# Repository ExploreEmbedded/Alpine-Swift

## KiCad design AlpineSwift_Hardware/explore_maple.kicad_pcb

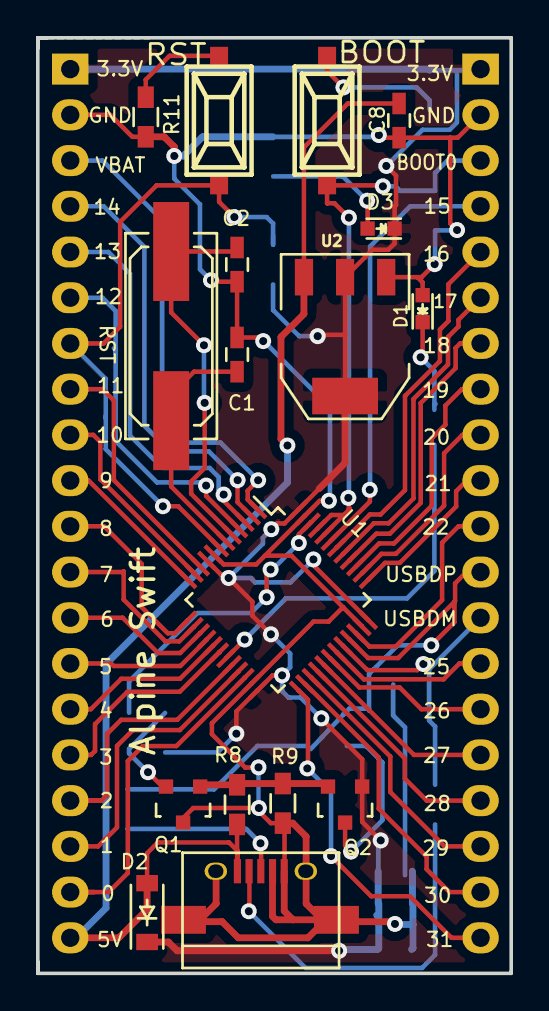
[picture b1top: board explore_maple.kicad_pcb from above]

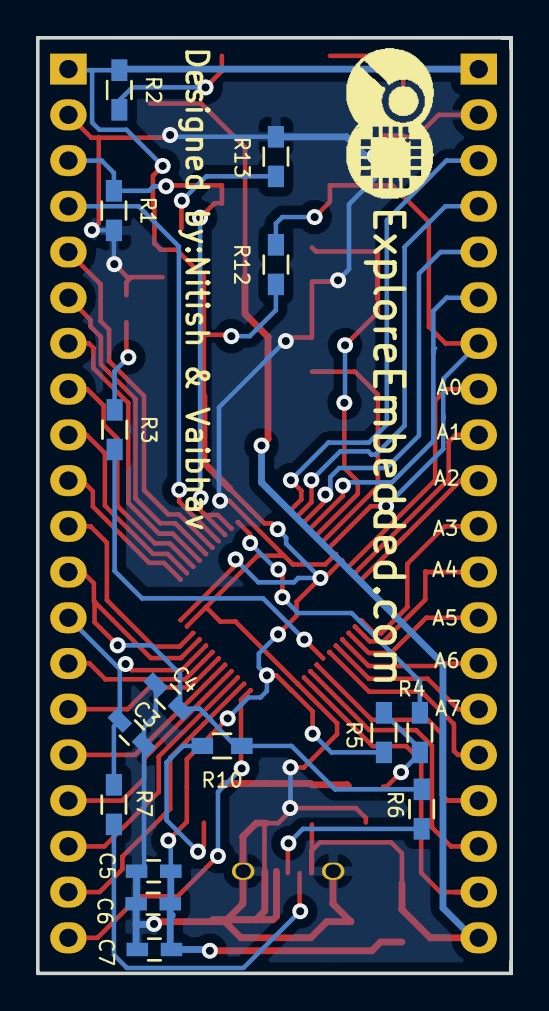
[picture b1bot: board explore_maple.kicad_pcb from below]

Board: 2 copper layers, 26.3 x 52.0 mm, 35 parts (16 on the bottom side), 51 nets.

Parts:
8MHZ1: CRYSTAL; Q_49U3HMS
BOOT: SPST; smd_push
C1, C2: 18pF; C_0603_HandSoldering
C3, C4: 47pf; C_0603_HandSoldering
C5, C6, C7: .1uF; C_0603_HandSoldering
C8: 100uF; C_0603_HandSoldering
CON1: USB-MICRO-B; USB_Micro-B
D1, D3: LED; LED-0603
D2: DIODE; SOD-123
LOGO: LOGO (2)
P1, P2: CONN_01X20; Pin_Header_Straight_1x20
Q1, Q2: BC547; SOT-23
R1, R8, R12: 10K; R_0603_HandSoldering
R2, R3, R4, R11: 1K; R_0603_HandSoldering
R5: 47K; R_0603_HandSoldering
R6, R7: 22; R_0603_HandSoldering
R9: 36K; R_0603_HandSoldering
R10: 1.5K; R_0603_HandSoldering
R13: 470; R_0603_HandSoldering
RST: SPST; smd_push
U1: STM32F103C8; LQFP-48_7x7mm_Pitch0.5mm
U2: LMNEW; SOT-223

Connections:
+3.3VP: C5.2, C6.2, C7.2, D2.1, D3.1, P1.1, P2.1, Q2.1, R2.1, R5.2, R12.1, U1.9, U1.24, U1.36, U1.48, U2.2, U2.4
+5V: C8.1, CON1.1, D2.2, P1.20, R8.2, U2.3
/10: P1.8, U1.10
/11: P1.9, U1.11
/12: P1.10, U1.12
/13: P1.11, U1.13
/14: P1.12, U1.14
/15: P1.13, U1.15
/16: P1.14, U1.16
/17: P1.15, U1.17
/25: P2.20, U1.25
/26: P2.19, U1.26
/27: P2.18, U1.27
/28: P2.17, U1.28
/37: P2.10, U1.37
/38: P2.9, U1.38
/39: P2.8, U1.39
/40: P2.7, U1.40
/41: P2.6, U1.41
/42: P2.5, U1.42
/43: P2.4, U1.43
/44: BOOT.1, P2.3, R1.1, U1.44, U1.45
/DISC: R4.2, U1.46
/OSC_IN: 8MHZ1.2, C2.1, U1.5
/OSC_OUT: 8MHZ1.1, C1.1, U1.6
/RESET: P1.7, R12.2, RST.2, U1.7
/USB_DM: C3.1, P2.13, R7.1, U1.32
/USB_DP: C4.1, P2.12, R6.1, R10.1, U1.33
GND: C1.2, C2.2, C3.2, C4.2, C5.1, C6.1, C7.1, C8.2, CON1.4, CON1.5, CON1.6, CON1.7, CON1.8, CON1.9, D1.2, P1.2, P2.2, Q1.3, R1.2, R9.1, R11.2, R13.2, U1.8, U1.23, U1.35, U1.47, U2.1
unnamed: BOOT.2, R2.2
unnamed: CON1.2, R7.2
unnamed: CON1.3, R6.2
unnamed: D1.1, R3.1
unnamed: D3.2, R13.1
unnamed: P1.3, U1.1
unnamed: P1.4, U1.2
unnamed: P1.5, U1.3
unnamed: P1.6, U1.4
unnamed: P1.16, U1.18
unnamed: P1.17, U1.20
unnamed: P1.18, U1.21
unnamed: P1.19, U1.22
unnamed: P2.11, U1.34
unnamed: P2.14, U1.31
unnamed: P2.15, U1.30
unnamed: P2.16, U1.29
unnamed: Q1.1, Q2.2, R8.1, R9.2
unnamed: Q1.2, R4.1, R5.1
unnamed: Q2.3, R10.2
unnamed: R3.2, U1.19
unnamed: R11.1, RST.1

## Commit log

2015-12-15 Alpineswift_Hardware
    Kicad hardware design files of Alpine Swift
2015-12-15 AlpineSwift_ArduinoSupport
    Add Arduino_STM32-master folder under hardware foldre of Arduino to get
    Arduino support for Alpine Swift.
2017-08-28 added board image
